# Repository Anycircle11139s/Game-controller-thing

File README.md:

STEP FILE:
https://drive.google.com/file/d/1q7aepsTQnkLOloDX4E2i3pMCJ2lylLdX/view?usp=sharing

# Game controller thing

So I just spent a really, really long time buiding a handheld game because my friend said hed let me have some golen gaytime if I designed and built a game :D

I created a custom PCB, firmware and a CAD case which I am really proud of, and I can already see how my skills and experience have increased/progressed since I started at hack club (I wouldn't be able to do this before). I am really excited about the project and I can't wait till I can build it for myself.

<br>

<br>

<br>

<br>

<br>

<br>

<br>

<br>
BOM:
<br>

|Name            |Purpose                               |Quantity|Total Cost (USD)|Link                                                                                                                                                                                                                                                                                                                                                                                                                                                                                                                                                                                                                                                                                                                                              |Distributor    |
|----------------|--------------------------------------|--------|----------------|--------------------------------------------------------------------------------------------------------------------------------------------------------------------------------------------------------------------------------------------------------------------------------------------------------------------------------------------------------------------------------------------------------------------------------------------------------------------------------------------------------------------------------------------------------------------------------------------------------------------------------------------------------------------------------------------------------------------------------------------------|---------------|
|pcb             |the pcb cause yes                     |        |9.53            |                                                                                                                                                                                                                                                                                                                                                                                                                                                                                                                                                                                                                                                                                                                                                  |jlcpcb         |
|lipo battery    |to power the thing                    |1       |4.85            |https://www.aliexpress.com/item/1005009733618301.html?spm=a2g0o.productlist.main.1.4dbf2bcdSIN130&algo_pvid=609a5463-33c2-4716-a65a-d027765c406e&algo_exp_id=609a5463-33c2-4716-a65a-d027765c406e-37&pdp_ext_f=%7B%22order%22%3A%2220%22%2C%22eval%22%3A%221%22%2C%22fromPage%22%3A%22search%22%7D&pdp_npi=6%40dis%21USD%218.81%214.85%21%21%218.81%214.85%21%402101c44f17775182871705306ea1b7%2112000049983242399%21sea%21AU%217402515296%21X%211%210%21n_tag%3A-29919%3Bd%3Aef1e07f3%3Bm03_new_user%3A-29895&curPageLogUid=ncMamPYHJDWc&utparam-url=scene%3Asearch%7Cquery_from%3A%7Cx_object_id%3A1005009733618301%7C_p_origin_prod%3A                                                                                                         |ali express    |
|ads1115         |for slider and joystick               |1       |3.27            |https://www.aliexpress.com/item/4000116831589.html?spm=a2g0o.productlist.main.4.e4367170pqiJeh&algo_pvid=54b18df7-b4a7-4482-b792-d480d9cb0b9a&aem_p4p_detail=202604241740286255615724926120001424947&algo_exp_id=54b18df7-b4a7-4482-b792-d480d9cb0b9a-3&pdp_ext_f=%7B%22order%22%3A%22359%22%2C%22eval%22%3A%221%22%2C%22fromPage%22%3A%22search%22%7D&pdp_npi=6%40dis%21USD%213.63%213.27%21%21%213.63%213.27%21%402101eee917770776282871616e7bde%2112000031353532263%21sea%21AU%217402515296%21X%211%210%21n_tag%3A-29911%3Bd%3Aef1e07f3%3Bm03_new_user%3A-29895&curPageLogUid=sNNybvIUvGwU&utparam-url=scene%3Asearch%7Cquery_from%3A%7Cx_object_id%3A4000116831589%7C_p_origin_prod%3A&search_p4p_id=202604241740286255615724926120001424947_1|ali express    |
|rotary encoder  |turning input                         |1       |1.27            |https://www.aliexpress.com/item/1005007644083514.html?spm=a2g0o.productlist.main.1.7b187465T0x8DI&algo_pvid=dd42beb6-a89c-4e9a-822a-aee0d3bb8655&algo_exp_id=dd42beb6-a89c-4e9a-822a-aee0d3bb8655-0&pdp_ext_f=%7B%22order%22%3A%222833%22%2C%22spu_best_type%22%3A%22price%22%2C%22eval%22%3A%221%22%2C%22fromPage%22%3A%22search%22%7D&pdp_npi=6%40dis%21USD%211.17%210.99%21%21%211.17%210.99%21%402101ee6617770766332183942e6637%2112000041630839415%21sea%21AU%217402515296%21X%211%210%21n_tag%3A-29911%3Bd%3Aef1e07f3%3Bm03_new_user%3A-29895%3BpisId%3A5000000204047332&curPageLogUid=TOJyxlb254yR&utparam-url=scene%3Asearch%7Cquery_from%3A%7Cx_object_id%3A1005007644083514%7C_p_origin_prod%3A                                         |ali express    |
|switches        |buttons                               |1       |3.33            |https://www.aliexpress.com/item/1005006425450443.html?mp=1&pdp_npi=6@dis!USD!USD+8.40!USD+0.99!!USD+0.99!!!@2101e2b417770755354165492e1519!12000037120671470!ct!AU!7402515296!!1!0!                                                                                                                                                                                                                                                                                                                                                                                                                                                                                                                                                               |ali express    |
|slide pot       |sliders                               |1       |2.66            |https://www.aliexpress.com/item/1005008713345793.html?spm=a2g0o.productlist.main.2.60983Pyu3PyuP1&algo_pvid=b0022195-0b79-4524-aa97-ece731d8ad54&algo_exp_id=b0022195-0b79-4524-aa97-ece731d8ad54-1&pdp_ext_f=%7B%22order%22%3A%22681%22%2C%22eval%22%3A%221%22%2C%22fromPage%22%3A%22search%22%7D&pdp_npi=6%40dis%21USD%212.66%210.99%21%21%2118.09%216.73%21%402101ee6617771813279241737e662c%2112000046545295127%21sea%21AU%217402515296%21X%211%210%21n_tag%3A-29911%3Bd%3Aef1e07f3%3Bm03_new_user%3A-29895%3BpisId%3A5000000204047332&curPageLogUid=FXsnTpFwKMfe&utparam-url=scene%3Asearch%7Cquery_from%3A%7Cx_object_id%3A1005008713345793%7C_p_origin_prod%3A                                                                             |ali express    |
|joystick        |a stick that gives out joy            |1       |2.25            |https://www.aliexpress.com/item/1005006375332797.html?spm=a2g0o.productlist.main.15.5f8999mT99mTyR&algo_pvid=a52f8a2f-d575-4ad3-bee8-e1a1bf34a230&algo_exp_id=a52f8a2f-d575-4ad3-bee8-e1a1bf34a230-12&pdp_ext_f=%7B%22order%22%3A%221642%22%2C%22eval%22%3A%221%22%2C%22fromPage%22%3A%22search%22%7D&pdp_npi=6%40dis%21USD%215.56%210.99%21%21%2137.82%216.70%21%40210328db17771815335367219ee95e%2112000037014017250%21sea%21AU%217402515296%21X%211%210%21n_tag%3A-29911%3Bd%3Aef1e07f3%3Bm03_new_user%3A-29895%3BpisId%3A5000000204047332&curPageLogUid=3UEUdfj2OnjF&utparam-url=scene%3Asearch%7Cquery_from%3A%7Cx_object_id%3A1005006375332797%7C_p_origin_prod%3A                                                                          |ali express    |
|100r resistor   |resisting                             |1       |2.27            |https://www.aliexpress.com/item/1005011767578775.html?spm=a2g0o.productlist.main.1.76e6ZlYYZlYY3F&algo_pvid=f206bbe8-b6cf-4d97-9d89-c2e8b83d0c2a&algo_exp_id=f206bbe8-b6cf-4d97-9d89-c2e8b83d0c2a-0&pdp_ext_f=%7B%22order%22%3A%22406%22%2C%22eval%22%3A%221%22%2C%22fromPage%22%3A%22search%22%7D&pdp_npi=6%40dis%21USD%212.25%212.25%21%21%2115.27%2115.27%21%402101e62517775175047942601ec187%2112000056498243033%21sea%21AU%217402515296%21X%211%210%21n_tag%3A-29919%3Bd%3Aef1e07f3%3Bm03_new_user%3A-29895&curPageLogUid=AbMFjAyFlsHa&utparam-url=scene%3Asearch%7Cquery_from%3A%7Cx_object_id%3A1005011767578775%7C_p_origin_prod%3A                                                                                                       |ali express    |
|4.7k resistor   |resisting                             |1       |2.27            |https://www.aliexpress.com/item/1005011767578775.html?spm=a2g0o.productlist.main.1.76e6ZlYYZlYY3F&algo_pvid=f206bbe8-b6cf-4d97-9d89-c2e8b83d0c2a&algo_exp_id=f206bbe8-b6cf-4d97-9d89-c2e8b83d0c2a-0&pdp_ext_f=%7B%22order%22%3A%22406%22%2C%22eval%22%3A%221%22%2C%22fromPage%22%3A%22search%22%7D&pdp_npi=6%40dis%21USD%212.25%212.25%21%21%2115.27%2115.27%21%402101e62517775175047942601ec187%2112000056498243033%21sea%21AU%217402515296%21X%211%210%21n_tag%3A-29919%3Bd%3Aef1e07f3%3Bm03_new_user%3A-29895&curPageLogUid=AbMFjAyFlsHa&utparam-url=scene%3Asearch%7Cquery_from%3A%7Cx_object_id%3A1005011767578775%7C_p_origin_prod%3A                                                                                                       |ali express    |
|oled            |display                               |1       |3.28            |https://www.aliexpress.com/item/1005006141235306.html?spm=a2g0o.productlist.main.5.3f1d5aQB5aQBoF&algo_pvid=df8c57ed-aec9-4026-bcdc-6001e1653fcb&algo_exp_id=df8c57ed-aec9-4026-bcdc-6001e1653fcb-4&pdp_ext_f=%7B%22order%22%3A%2224858%22%2C%22spu_best_type%22%3A%22price%22%2C%22eval%22%3A%221%22%2C%22fromPage%22%3A%22search%22%7D&pdp_npi=6%40dis%21USD%213.28%213.28%21%21%2122.31%2122.31%21%40210328d417775169223114674e3f7a%2112000035944225407%21sea%21AU%217402515296%21X%211%210%21n_tag%3A-29919%3Bd%3Aef1e07f3%3Bm03_new_user%3A-29895&curPageLogUid=PcB4MSEwSkfi&utparam-url=scene%3Asearch%7Cquery_from%3A%7Cx_object_id%3A1005006141235306%7C_p_origin_prod%3A                                                                 |ali express    |
|100nF capacitors|capacitors                            |1       |2.45            |https://www.aliexpress.com/item/1005011747293156.html?spm=a2g0o.productlist.main.2.5d0cW9aYW9aYN6&algo_pvid=49c092ae-32d3-499e-9581-dbbdd42c5039&algo_exp_id=49c092ae-32d3-499e-9581-dbbdd42c5039-1&pdp_ext_f=%7B%22order%22%3A%22885%22%2C%22eval%22%3A%221%22%2C%22fromPage%22%3A%22search%22%7D&pdp_npi=6%40dis%21USD%211.90%211.90%21%21%2112.93%2112.93%21%402101eee917775168025443418ef2eb%2112000056423315138%21sea%21AU%217402515296%21X%211%210%21n_tag%3A-29919%3Bd%3Aef1e07f3%3Bm03_new_user%3A-29895&curPageLogUid=lGNuhkprjgKw&utparam-url=scene%3Asearch%7Cquery_from%3A%7Cx_object_id%3A1005011747293156%7C_p_origin_prod%3A                                                                                                       |Ali express    |
|Buzzer          |for noise                             |1       |1.90            |https://www.aliexpress.com/item/1005007760117171.html?spm=a2g0o.productlist.main.3.6030mV5emV5e3L&algo_pvid=eef0c9b7-e91c-4ed5-b4f4-4c7a828aafc4&algo_exp_id=eef0c9b7-e91c-4ed5-b4f4-4c7a828aafc4-2&pdp_ext_f=%7B%22order%22%3A%2249%22%2C%22eval%22%3A%221%22%2C%22fromPage%22%3A%22search%22%7D&pdp_npi=6%40dis%21USD%212.87%210.99%21%21%2119.49%216.70%21%402103129f17771804952892675e59d3%2112000042136775304%21sea%21AU%217402515296%21X%211%210%21n_tag%3A-29911%3Bd%3Aef1e07f3%3Bm03_new_user%3A-29895%3BpisId%3A5000000204047332&curPageLogUid=3fwWn3qz4T5N&utparam-url=scene%3Asearch%7Cquery_from%3A%7Cx_object_id%3A1005007760117171%7C_p_origin_prod%3A                                                                              |ali express    |
|the case        |slick af thing that everything goes in|1       |6.50            |                                                                                                                                                                                                                                                                                                                                                                                                                                                                                                                                                                                                                                                                                                                                                  |printing legion|
|xiao esp32 s3   |microcontroller                       |1       |10.70           |https://www.aliexpress.com/item/1005005543738460.html?spm=a2g0o.productlist.main.9.548423233N4hX9&algo_pvid=40a65dd5-e78b-4226-898b-bc6857bc487d&algo_exp_id=40a65dd5-e78b-4226-898b-bc6857bc487d-8&pdp_ext_f=%7B%22order%22%3A%22312%22%2C%22eval%22%3A%221%22%2C%22fromPage%22%3A%22search%22%7D&pdp_npi=6%40dis%21USD%2110.18%217.53%21%21%2110.18%217.53%21%402101e2b217775214525851376e0541%2112000033478832279%21sea%21AU%217402515296%21X%211%210%21n_tag%3A-29919%3Bd%3Aef1e07f3%3Bm03_new_user%3A-29895&curPageLogUid=AiLlLlucd8qa&utparam-url=scene%3Asearch%7Cquery_from%3A%7Cx_object_id%3A1005005543738460%7C_p_origin_prod%3A                                                                                                       |ali express    |

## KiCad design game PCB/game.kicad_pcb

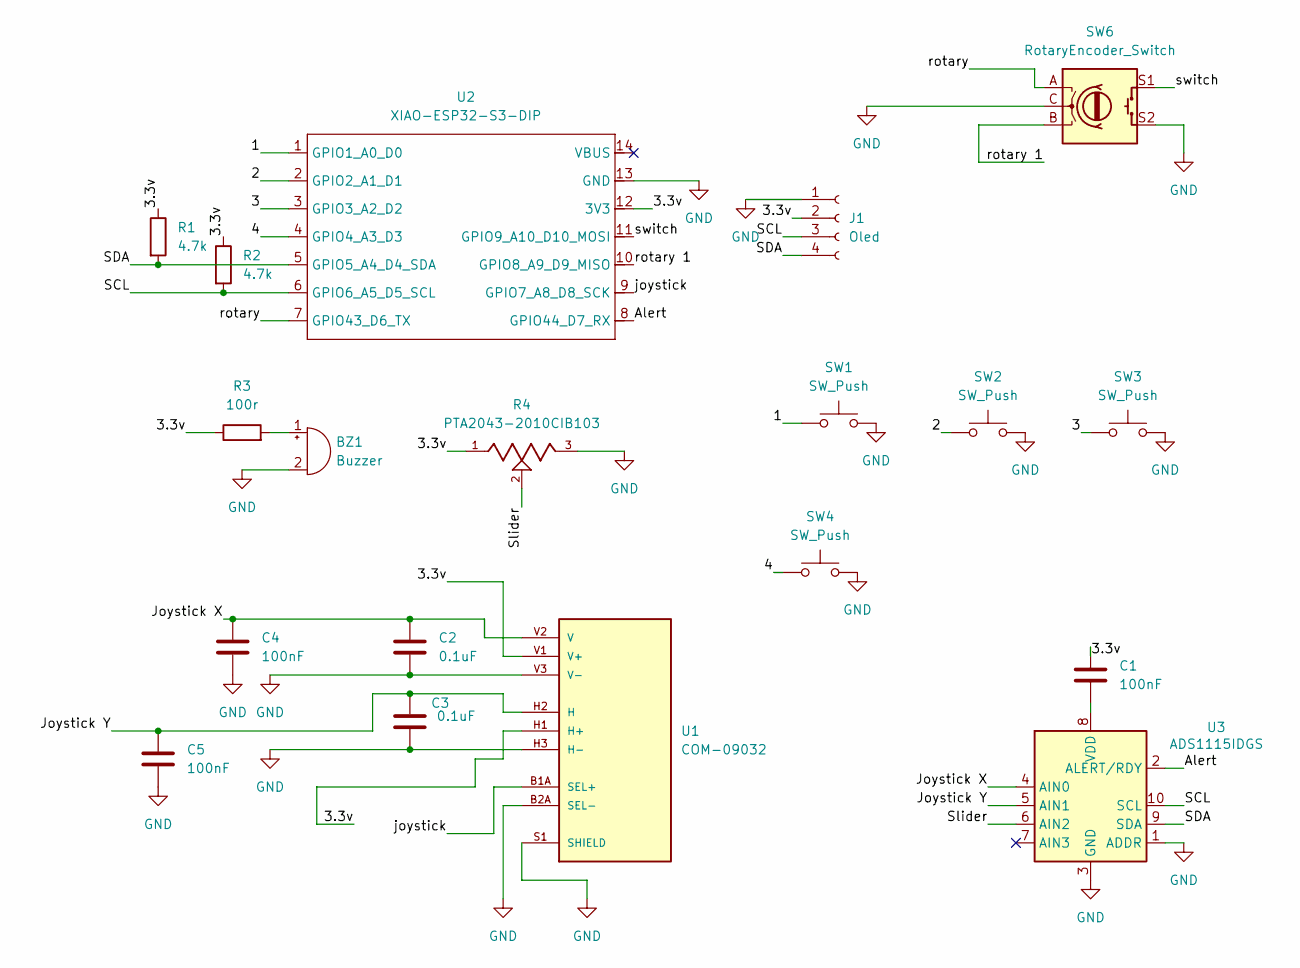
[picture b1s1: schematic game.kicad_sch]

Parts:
BZ1: Buzzer; Buzzer_12x9.5RM7.6
C1, C4, C5: 100nF; C_Disc_D3.0mm_W1.6mm_P2.50mm
C2, C3: 0.1uF; C_Disc_D3.0mm_W1.6mm_P2.50mm
J1: Oled; PinHeader_1x04_P2.54mm_Vertical
R1, R2: 4.7k; R_Axial_DIN0207_L6.3mm_D2.5mm_P7.62mm_Horizontal
R3: 100r; R_Axial_DIN0207_L6.3mm_D2.5mm_P7.62mm_Horizontal
R4: PTA2043-2010CIB103; TRIM_PTA2043-2010CIB103; PARTREV 04/21
SW1, SW2, SW3, SW4: SW_Push; SW_Cherry_MX_1.00u_PCB
SW6: RotaryEncoder_Switch; RotaryEncoder_Alps_EC11E-Switch_Vertical_H20mm
U1: COM-09032; XDCR_COM-09032; PARTREV N/A
U2: XIAO-ESP32-S3-DIP
U3: ADS1115IDGS; TSSOP-10_3x3mm_P0.5mm

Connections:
/1: SW1.1, U2.1 (GPIO1_A0_D0)
/2: SW2.1, U2.2 (GPIO2_A1_D1)
/3: SW3.1, U2.3 (GPIO3_A2_D2)
/3.3v: C1.1, J1.2, R1.1, R2.1, R3.1, R4.1, U1.H1 (H+), U1.V1 (V+), U2.12 (3V3)
/4: SW4.1, U2.4 (GPIO4_A3_D3)
/Alert: U2.8 (GPIO44_D7_RX), U3.2 (ALERT/RDY)
/Joystick X: C2.1, C4.2, U1.V2 (V), U3.4 (AIN0)
/Joystick Y: C3.1, C5.2, U1.H2 (H), U3.5 (AIN1)
/SCL: J1.3, R2.2, U2.6 (GPIO6_A5_D5_SCL), U3.10 (SCL)
/SDA: J1.4, R1.2, U2.5 (GPIO5_A4_D4_SDA), U3.9 (SDA)
/Slider: R4.2, U3.6 (AIN2)
/joystick: U1.B1A (SEL+), U2.9 (GPIO7_A8_D8_SCK)
/rotary: SW6.A, U2.7 (GPIO43_D6_TX)
/rotary 1: SW6.B, U2.10 (GPIO8_A9_D9_MISO)
/switch: SW6.S1, U2.11 (GPIO9_A10_D10_MOSI)
GND: BZ1.2 (-), C2.2, C3.2, C4.1, C5.1, J1.1, R4.3, SW1.2, SW2.2, SW3.2, SW4.2, SW6.C, SW6.S2, U1.B2A (SEL-), U1.H3 (H-), U1.S1 (SHIELD), U1.S2 (SHIELD), U1.S3 (SHIELD), U1.S4 (SHIELD), U1.V3 (V-), U2.13 (GND), U3.1 (ADDR), U3.3 (GND)
unnamed: BZ1.1 (+), R3.2
unnamed: C1.2, U3.8 (VDD)

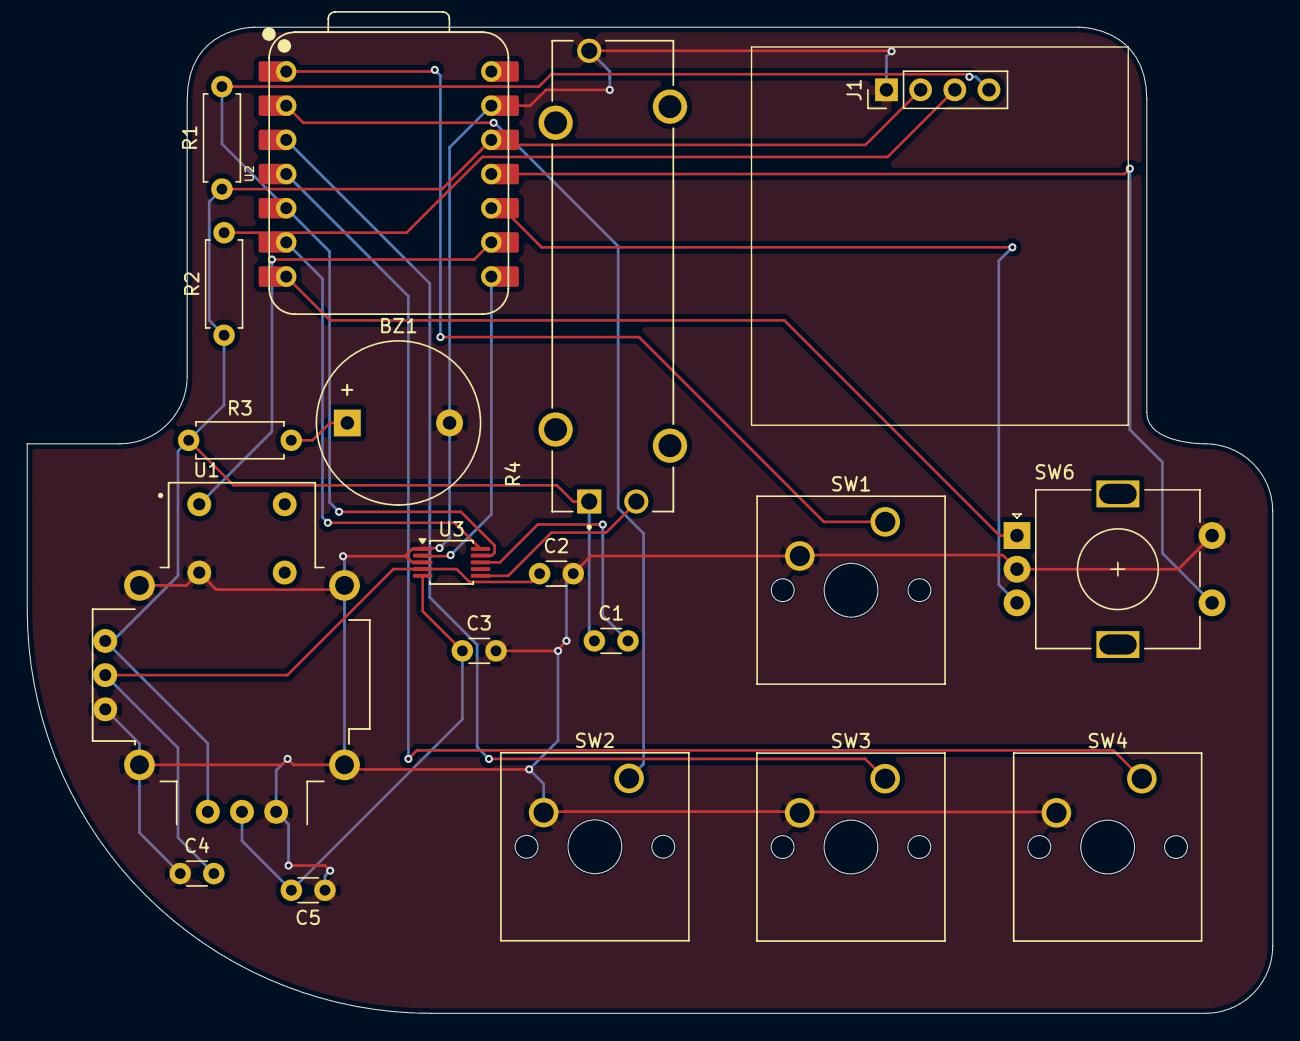
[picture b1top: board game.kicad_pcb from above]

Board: 2 copper layers, 92.6 x 73.3 mm, 19 parts (0 on the bottom side), 18 nets.
